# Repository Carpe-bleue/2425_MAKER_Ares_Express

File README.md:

# 2425_MAKER_Ares_Express
Depository for the "Ares Express" project, within the framework of the Maker option of ENSEA led by M.Papazoglou

Video récapitulative : https://www.youtube.com/watch?v=NGvs9T8YtXU

# Description
The idea of this project is to build a miniature train on rails. It would integrate features like LEDs, sound, moving parts, screen(s), storage capacity, and remote controlled.
The PCB and motors would be placed in the head Wagon in the front and other wagons would be attached to it and could be replaced easily so we would switch them depending what we want the train to do (adding wagons that can contain things or just fun or decorative wagons).

from the following video : "https://youtu.be/WkL9zbtfKDo?si=UJvP77D1sXWMVc81"

# For now :
https://github.com/user-attachments/assets/c41e23c4-729e-4bb9-a937-4c54bc4e76e5

# Ideas

- wheels :
- 

- module HC-SR04 (detect obstacles) :
- 
  
- Steam ? :
- 

PCB : moteurs (x2 minimum), battery, communication module (bluetooth ?), ultrasound module, screen, actuators, module that make sound ?, LEDs, electro-magnets ?, accelerometers, 

electromagnets to attach/detach wagons !
Camera ?

- details : angry eyebrows, ares logo, small characters ?
Difficult ideas : A claw to move an object from the tracks, mapping room with lidar, putting tracks before itself, Stations

# Planning :

- 3d Model, 1st wagon : 23 janvier
- Printing 1st Wagon : 23-27 janvier
- PCB : 10 février

- Vacation : Models for Head wagon and rails

- 1st rail (laser) : 3 mars
- Head wagon model : 10 mars
- Printing head Wagon : 13 mars
- Test of head wagon with PCB : 17 mars 
- Complete track (laser cut wood) : 20 mars-24 mars
- Soft (screen, LEDs, communication) : 27 mars - 4 avril

Module Hc-sr04 :

Module Hc-05 : 

Module Caméra ? :

Potentially useful regulator :

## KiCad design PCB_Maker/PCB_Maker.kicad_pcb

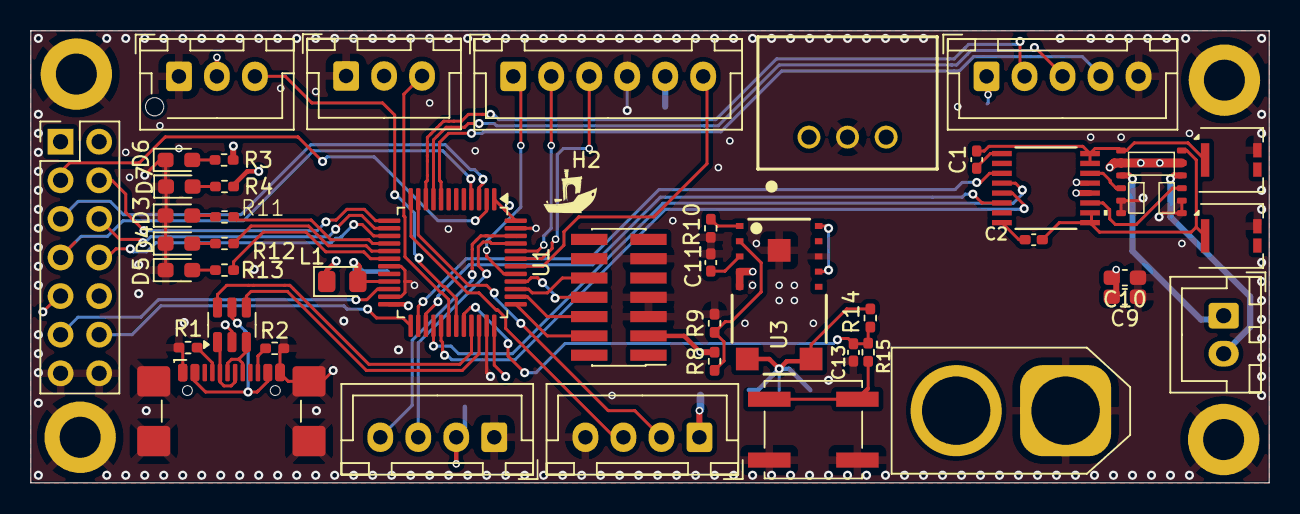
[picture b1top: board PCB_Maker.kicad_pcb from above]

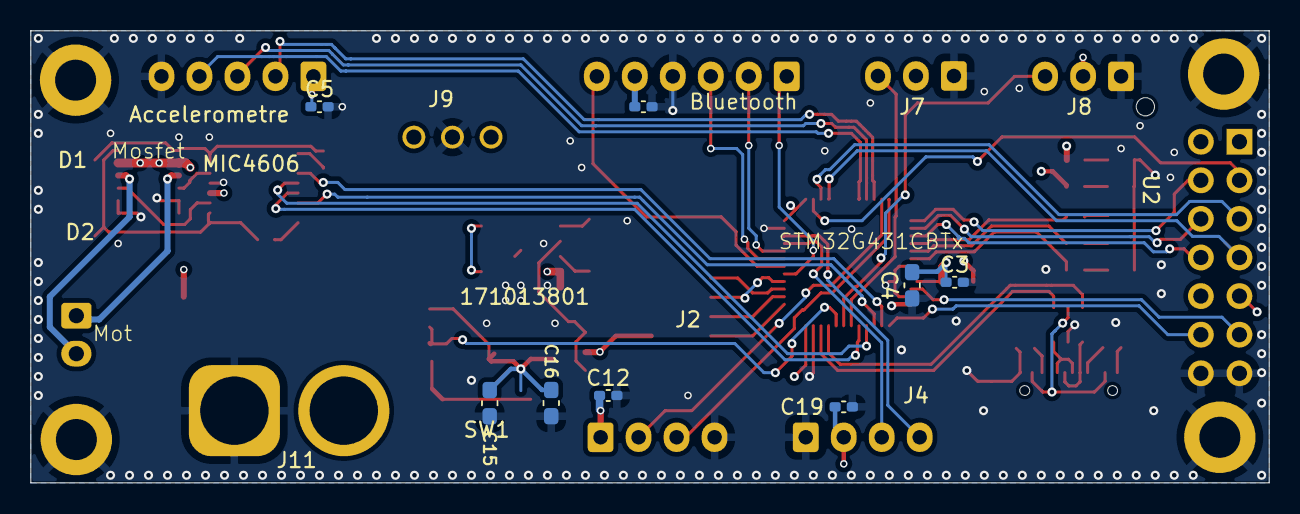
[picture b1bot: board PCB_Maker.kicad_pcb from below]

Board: 4 copper layers, 81.5 x 29.8 mm, 56 parts (8 on the bottom side), 63 nets.

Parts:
C1, C2, C5, C6, C11, C12, C19: 1u; C_0402_1005Metric_Pad0.74x0.62mm_HandSolder
C3, C13: 10n; C_0402_1005Metric_Pad0.74x0.62mm_HandSolder
C4: 1u; C_0603_1608Metric_Pad1.08x0.95mm_HandSolder
C9: 22u; C_0603_1608Metric_Pad1.08x0.95mm_HandSolder
C10: 10u; C_0603_1608Metric_Pad1.08x0.95mm_HandSolder
C15, C16: 100n; C_0603_1608Metric_Pad1.08x0.95mm_HandSolder
D1, D2: D_Zener; Littelfuse_PolyZen-LS
D3, D4, D5: LED_GREEN; LED_0603_1608Metric_Pad1.05x0.95mm_HandSolder
D6: RED_LED_5V; LED_0603_1608Metric_Pad1.05x0.95mm_HandSolder
D7: RED_LED_3.3V; LED_0603_1608Metric_Pad1.05x0.95mm_HandSolder
H1, H2, H3, H4: MountingHole_Pad; MountingHole_2.7mm_M2.5_DIN965_Pad
J1: USB_C_Receptacle_USB2.0_16P; USB_C_Receptacle_GCT_USB4110
J2: Conn_ST_STDC14; PinHeader_2x07_P1.27mm_Vertical_SMD
J3: Conn_01x02; JST_XH_B2B-XH-A_1x02_P2.50mm_Vertical
J4, J5: Conn_01x04; JST_XH_B4B-XH-A_1x04_P2.50mm_Vertical
J6: Conn_01x05; JST_XH_B5B-XH-A_1x05_P2.50mm_Vertical
J7: Conn_01x03; JST_XH_B3B-XH-A_1x03_P2.50mm_Vertical
J8: Conn_01x03; JST_XH_B3B-XH-AM_1x03_P2.50mm_Vertical
J9: 173010542; 173013542
J10: Conn_02x07_Odd_Even; PinHeader_2x07_P2.54mm_Vertical
J11: Conn_01x02; AMASS_XT60-F_1x02_P7.20mm_Vertical
J12: Conn_01x06; JST_XH_B6B-XH-A_1x06_P2.50mm_Vertical
L1: 39n; LED_0805_2012Metric_Pad1.15x1.40mm_HandSolder
MIC4606: TSSOP16_TS_MCH_MIS
Mosfet_canal_N1: FDMQ86530L
R1, R2: 5.1k; R_0402_1005Metric_Pad0.72x0.64mm_HandSolder
R3: 3k6; R_0402_1005Metric_Pad0.72x0.64mm_HandSolder
R4, R11, R12, R13: 1k6; R_0402_1005Metric_Pad0.72x0.64mm_HandSolder
R8: 287k; R_0402_1005Metric_Pad0.72x0.64mm_HandSolder
R9: 137k; R_0402_1005Metric_Pad0.72x0.64mm_HandSolder
R10: 5.6k; R_0402_1005Metric_Pad0.72x0.64mm_HandSolder
R14, R15: 10k; R_0402_1005Metric_Pad0.72x0.64mm_HandSolder
SW1: SW_Push; SW_Push_1P1T_NO_CK_KSC6xxJ
U1: STM32G431CBTx; LQFP-48_7x7mm_P0.5mm
U2: USBLC6-2SC6; SOT-23-6
U3: 171013801; 171023801

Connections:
+3.3V: C12.1, C15.1, C16.1, C19.1, J2.3 (VCC), J4.2, J5.1, J10.9, J10.10, L1.1, R4.1, R8.1, R14.1, U1.1 (VBAT), U1.24 (VDD), U1.36 (VDD), U1.48 (VDD), U3.6, U3.7
+3.3VA: C3.1, C4.1, L1.2, U1.21 (VDDA)
+5V: C5.1, C6.1, J6.1, J7.2, J8.2, J9.3 (VOUT), J10.1, J10.2, J12.5, R3.1
/ADC_accelerometer_X: J6.2, U1.10 (PA2)
/ADC_accelerometer_Y: J6.3, U1.9 (PA1)
/ADC_accelerometer_Z: J6.4, U1.8 (PA0)
/D+: J1.A6 (D+), J1.B6 (D+), U2.3 (I/O2)
/D-: J1.A7 (D-), J1.B7 (D-), U2.1 (I/O1)
/EN_Bluetooth: J12.6, U1.42 (PB5)
/Echo_HC_SR04: J5.3, U1.12 (PA4)
/GPIO_filtered: C13.1, R14.2, R15.1, U1.32 (PA10)
/I2C1_SCL: J4.3, U1.45 (PB8)
/I2C1_SDA: J4.4, U1.46 (PB9)
/PA_5: J10.4, U1.13 (PA5)
/PA_6: J10.6, U1.14 (PA6)
/PA_7: J10.8, U1.15 (PA7)
/PB0_LED_1: R11.1, U1.16 (PB0)
/PB1_LED_2: R12.1, U1.17 (PB1)
/PB2_LED_3: R13.1, U1.18 (PB2)
/PB_10: J10.11, U1.22 (PB10)
/PB_11: J10.12, U1.25 (PB11)
/PC_13: J10.3, U1.2 (PC13)
/PC_14: J10.5, U1.3 (PC14)
/PC_15: J10.7, U1.4 (PC15)
/PWM_TIM1_CH1: J7.3, U1.30 (PA8)
/PWM_TIM1_CH2: J8.3, U1.31 (PA9)
/STATE_Bluetooth: J12.1, U1.41 (PB4)
/Trig_HC-SR04: J5.2, U1.11 (PA3)
/USART1_RX: J12.2, U1.44 (PB7)
/USART1_TX: J12.3, U1.43 (PB6)
/USB_DM: U1.33 (PA11), U2.6 (I/O1)
/USB_DP: U1.34 (PA12), U2.4 (I/O2)
/V_USB: J1.A4 (VBUS), J1.A9 (VBUS), J1.B4 (VBUS), J1.B9 (VBUS), U2.5 (VBUS)
AHI: MIC4606.6 (AHI), U1.27 (PB13)
AHO: C2.1, D2.1 (K), MIC4606.9 (AHO), MIC4606.10 (AHS), Mosfet_canal_N1.12 (G4)
ALI: MIC4606.5 (ALI), U1.29 (PB15)
ALO: MIC4606.11 (ALO), Mosfet_canal_N1.9 (G3)
BHI: MIC4606.3 (BHI), U1.26 (PB12)
BHO: C1.1, D1.1 (K), MIC4606.15 (BHS), MIC4606.16 (BHO), Mosfet_canal_N1.1 (G1)
BLI: MIC4606.4 (BLI), U1.28 (PB14)
BLO: MIC4606.14 (BLO), Mosfet_canal_N1.4 (G2)
GND: C3.2, C4.2, C5.2, C6.2, C9.1, C10.1, C11.2, C12.2, C13.2, C15.2, C16.2, C19.2, D1.2 (A), D2.2 (A), D3.1 (K), D4.1 (K), D5.1 (K), D6.1 (K), D7.1 (K), H1.1, H2.1, H3.1, H4.1, J1.A1 (GND), J1.A12 (GND), J1.B1 (GND), J1.B12 (GND), J1.S1 (SHIELD), J2.5 (GND), J2.7 (GND), J2.11 (GNDDetect), J4.1, J5.4, J6.5, J7.1, J8.1, J9.2 (GND), J10.13, J10.14, J11.1, J12.4, MIC4606.13 (VSS), Mosfet_canal_N1.5 (S2), Mosfet_canal_N1.6 (S2), Mosfet_canal_N1.7 (S3), Mosfet_canal_N1.8 (S3), R1.2, R2.2, R9.2, R10.1, SW1.2, U1.19 (VSSA), U1.23 (VSS), U1.35 (VSS), U1.47 (VSS), U2.2 (GND), U3.10, U3.EP
JTDI: J2.10 (JTDI/NC), U1.39 (PA15)
MOT_1: J3.1, Mosfet_canal_N1.3 (S1/D2)
MOT_2: J3.2, Mosfet_canal_N1.10 (D3/S4)
unnamed: C11.1, U3.3
unnamed: D3.2 (A), R11.2
unnamed: D4.2 (A), R12.2
unnamed: D5.2 (A), R13.2
unnamed: D6.2 (A), R3.2
unnamed: D7.2 (A), R4.2
unnamed: J1.A5 (CC1), R1.1
unnamed: J1.B5 (CC2), R2.1
unnamed: C2.2, MIC4606.8 (AHB)
unnamed: C1.2, MIC4606.1 (BHB)
unnamed: R8.2, R9.1, U3.2
unnamed: R10.2, U3.1
unnamed: R15.2, SW1.1
unnamed: U3.9, U3.12
SWCLK: J2.6 (JCLK/SWCLK), U1.38 (PA14)
SWDIO: J2.4 (JTMS/SWDIO), U1.37 (PA13)
SWO: J2.8 (JTDO/SWO), U1.40 (PB3)
VCC: C9.2, C10.2, J9.1 (VIN), J11.2, MIC4606.12 (VDD), Mosfet_canal_N1.2 (D1/D4), Mosfet_canal_N1.11 (D1/D4), U3.4, U3.5

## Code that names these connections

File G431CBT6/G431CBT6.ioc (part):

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Mcu.Name=STM32G431C(6-8-B)Tx
Mcu.Package=LQFP48
Mcu.UserName=STM32G431CBTx
PA0.Mode=IN1-Single-Ended
PA0.Signal=ADC1_IN1
PA1.Mode=IN2-Single-Ended
PA1.Signal=ADC1_IN2
PA10.Signal=GPIO_Output
PA11.Mode=Device
PA11.Signal=USB_DM
PA12.Mode=Device
PA12.Signal=USB_DP
PA13.Mode=JTAG_4_pins
PA13.Signal=SYS_JTMS-SWDIO
PA14.Mode=JTAG_4_pins
PA14.Signal=SYS_JTCK-SWCLK
PA15.Mode=JTAG_4_pins
PA15.Signal=SYS_JTDI
PA2.Mode=IN3-Single-Ended
PA2.Signal=ADC1_IN3
PA3.GPIOParameters=GPIO_Label
PA3.GPIO_Label=Trig
PA3.Signal=S_TIM2_CH4
PA4.GPIOParameters=GPIO_Label
PA4.GPIO_Label=Echo
PA4.Signal=S_TIM3_CH2
PA5.Signal=GPIO_Output
PA6.Signal=GPIO_Output
PA7.Signal=GPIO_Output
PA8.GPIOParameters=GPIO_Label
PA8.GPIO_Label=AHI
PA8.Signal=S_TIM1_CH1
PA9.GPIOParameters=GPIO_Label
PA9.GPIO_Label=BHI
PA9.Signal=S_TIM1_CH2
PB0.GPIOParameters=GPIO_Label
PB0.GPIO_Label=LED1
PB0.Signal=GPIO_Output
PB1.GPIOParameters=GPIO_Label
PB1.GPIO_Label=LED2
PB1.Signal=GPIO_Output
PB10.Signal=GPIO_Output
PB11.Signal=GPIO_Output
PB12.Signal=GPIO_Output
PB13.GPIOParameters=GPIO_Label
PB13.GPIO_Label=ALI
PB13.Mode=PWM Generation1 CH1 CH1N
PB13.Signal=TIM1_CH1N
PB14.GPIOParameters=GPIO_Label
PB14.GPIO_Label=BLI
PB14.Mode=PWM Generation2 CH2 CH2N
PB14.Signal=TIM1_CH2N
PB15.Signal=GPIO_Output
PB2.GPIOParameters=GPIO_Label
PB2.GPIO_Label=LED3
PB2.Signal=GPIO_Output
PB3.Mode=JTAG_4_pins
PB3.Signal=SYS_JTDO-SWO
PB4.GPIOParameters=GPIO_Label
PB4.GPIO_Label=State_Bluetooth
PB4.Signal=GPIO_Input
PB5.GPIOParameters=GPIO_Label
PB5.GPIO_Label=EN_Blutooth
PB5.Signal=GPIO_Output
PB6.Mode=Asynchronous
PB6.Signal=USART1_TX
PB7.Mode=Asynchronous
PB7.Signal=USART1_RX
PB8-BOOT0.Mode=I2C
PB8-BOOT0.Signal=I2C1_SCL
PB9.Mode=I2C
PB9.Signal=I2C1_SDA
PC13.Signal=GPIO_Output
PC14-OSC32_IN.Signal=GPIO_Output
PC15-OSC32_OUT.Signal=GPIO_Output
RCC.HSE_VALUE=8000000
RCC.SYSCLKFreq_VALUE=16000000
board=custom

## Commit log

2025-01-25 Ajouté(e) Diagramme sans nom.drawio
2025-01-26 Add photos 3D impression
2025-03-18 PCB_Train
2025-03-19 PCB improve
2025-03-20 projet stm
2025-03-20 pcb correction
2025-03-24 PCB correction Mr.Papazoglou
